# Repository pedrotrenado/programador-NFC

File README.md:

# Sistema Electrónico para la Actualización Firmware de Sensores vía NFC

Este proyecto tiene como objetivo el diseño e implementación de un sistema electrónico para la actualización del firmware de sensores a través de la tecnología NFC (Near Field Communication).

## Descripción del Proyecto
Ante la necesidad de mejorar el proceso de actualización de dispositivos de bajo consumo alimentados por baterías, se ha determinado que la mejor forma de llevar a cabo esta tarea es mediante NFC. Este sistema permitirá actualizar los sensores de manera eficiente y sin la necesidad de acceder físicamente a la PCB.

## Diseño de las PCB
Las placas de circuito impreso (PCB) han sido diseñadas utilizando la herramienta KiCad 7.

### Ejemplo de diseño
A continuación se muestra un ejemplo del diseño frontal y posterior de la PCB cuya antena NFC es del tamaño de la antena del sensor:
<div style="display: flex; justify-content: center; align-items: center; gap: 10px;">

</div>

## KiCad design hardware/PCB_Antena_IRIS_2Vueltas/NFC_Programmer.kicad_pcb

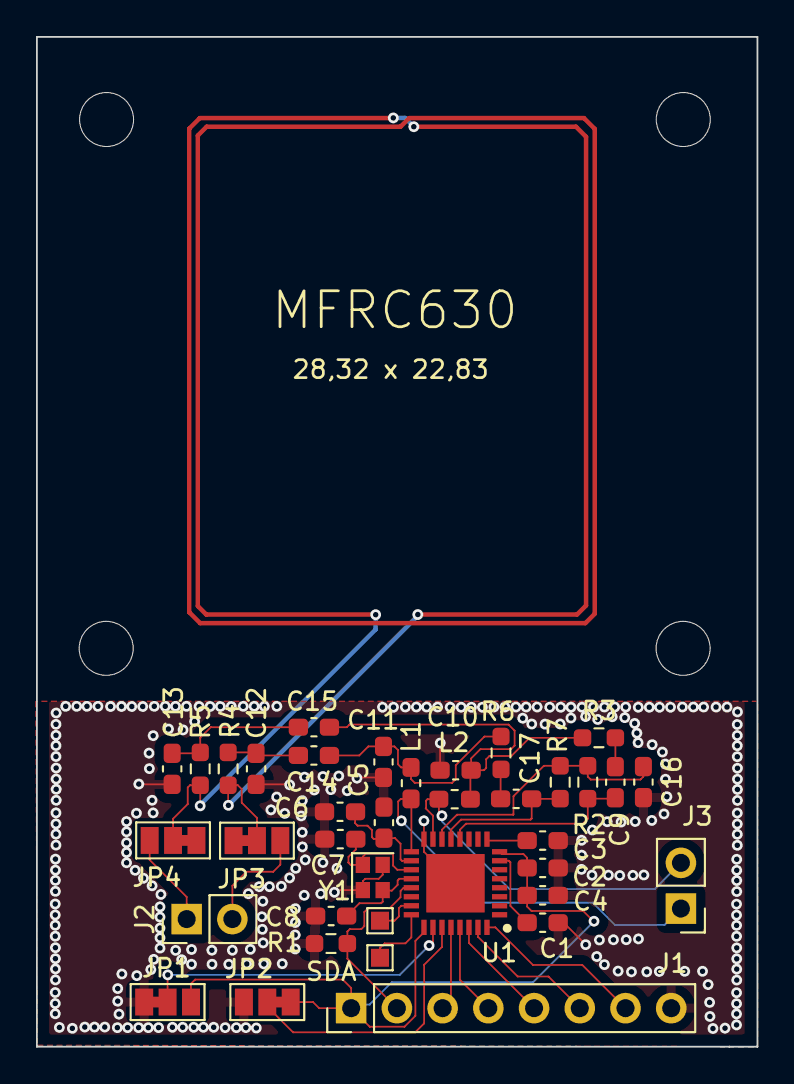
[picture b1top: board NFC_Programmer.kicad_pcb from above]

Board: 2 copper layers, 40.0 x 56.1 mm, 41 parts (0 on the bottom side), 31 nets.

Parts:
C1, C3: 470n; C_0603_1608Metric_Pad1.08x0.95mm_HandSolder
C2, C4, C5: 100n; C_0603_1608Metric_Pad1.08x0.95mm_HandSolder
C6: 1u; C_0603_1608Metric_Pad1.08x0.95mm_HandSolder
C7, C8: 10p; C_0603_1608Metric_Pad1.08x0.95mm_HandSolder
C9, C10, C11, C12, C13, C15, C16, C17: TBD; C_0603_1608Metric_Pad1.08x0.95mm_HandSolder
C14: C; C_0603_1608Metric_Pad1.08x0.95mm_HandSolder
H1, H2, H3, H4: MountingHole_Pad; MountingHole_3mm
J1: Conn_01x08; PinHeader_1x08_P2.54mm_Vertical
J2, J3: Conn_01x02_Pin; PinHeader_1x02_P2.54mm_Vertical
JP1, JP2, JP3, JP4: SolderJumper_3_Bridged12; SolderJumper-3_P1.3mm_Bridged12_Pad1.0x1.5mm_NumberLabels
L1, L2: TBD; L_0603_1608Metric_Pad1.05x0.95mm_HandSolder
R1: 10k; R_0603_1608Metric_Pad0.98x0.95mm_HandSolder
R2, R3, R4, R5, R6, R7: TBD; R_0603_1608Metric_Pad0.98x0.95mm_HandSolder
TP1, TP2: TestPoint; TestPoint_Pad_1.0x1.0mm
U1: MFRC63002HN,151; MFRC630_MOUSER
Y1: Crystal_27.12MHz; Crystal_SMD_2016-4Pin_2.0x1.6mm

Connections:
+3V3: C2.1, C4.1, J1.1, JP1.3 (B), JP2.1 (A), U1.8 (VDD), U1.25 (PVDD)
/IFSEL0: JP1.2 (C), U1.26 (IFSEL0)
/IFSEL1: JP2.2 (C), U1.27 (IFSEL1)
/IRQ: J1.7, U1.32 (IRQ)
/MISO: J1.5, U1.30 (IF2)
/MOSI: J1.3, U1.28 (IF0)
/NSS: J1.6, U1.31 (IF3)
/PDOWN: J1.2, R1.1, U1.21 (PDOWN)
/RXN: C17.1, R7.1, U1.13 (RXN)
/RXP: C9.1, R2.2, U1.12 (RXP)
/SCK: J1.4, U1.29 (IF1)
/SCL: TP2.1, U1.23 (SCL)
/SDA: TP1.1, U1.24 (SDA)
/TX1: J3.1, L1.1, U1.17 (TX1)
/TX2: J3.2, L2.1, U1.15 (TX2)
/VMID: C16.1, R2.1, R7.2, U1.14 (VMID)
GND: C1.2, C2.2, C3.2, C4.2, C5.2, C6.2, C7.2, C8.2, C10.1, C11.2, C12.2, C13.1, C16.2, J1.8, JP1.1 (A), JP2.3 (B), R1.2, U1.16 (TVSS), U1.33 (VSS), Y1.2, Y1.4
unnamed: C9.2, R3.2
unnamed: C10.2, C15.1, L2.2, R3.1
unnamed: C11.1, C14.1, L1.2, R6.2
unnamed: C12.1, C14.2, R4.1
unnamed: C13.2, C15.2, R5.1
unnamed: C17.2, R6.1
unnamed: J2.1, JP4.3 (B)
unnamed: J2.2, JP3.3 (B)
unnamed: JP3.2 (C), JP4.2 (C), R4.2, R5.2
unnamed: C3.1, U1.9 (AVDD)
unnamed: C1.1, U1.7 (DVDD)
unnamed: C5.1, C6.1, U1.18 (TVDD)
unnamed: C7.1, U1.19 (XTAL1), Y1.1
unnamed: C8.1, U1.20 (XTAL2), Y1.3

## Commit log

2024-02-02 NFC_Programmer/
2024-04-03 PCBs
2024-04-03 Carpeta Eliminada
2024-04-03 README
2024-04-16 nuevo diseño con pistas más anchas
2024-04-20 Actualización de los conectores
2024-04-22 MFRC630 python library development
2024-04-22 Images folder
2024-04-22 Hardware folder
2024-04-25 Actualización de conectores
2024-04-25 Imágenes de diseño de PCB
2024-04-29 Carpeta fw
2024-05-17 Actualizacion
2024-09-23 Software folder
